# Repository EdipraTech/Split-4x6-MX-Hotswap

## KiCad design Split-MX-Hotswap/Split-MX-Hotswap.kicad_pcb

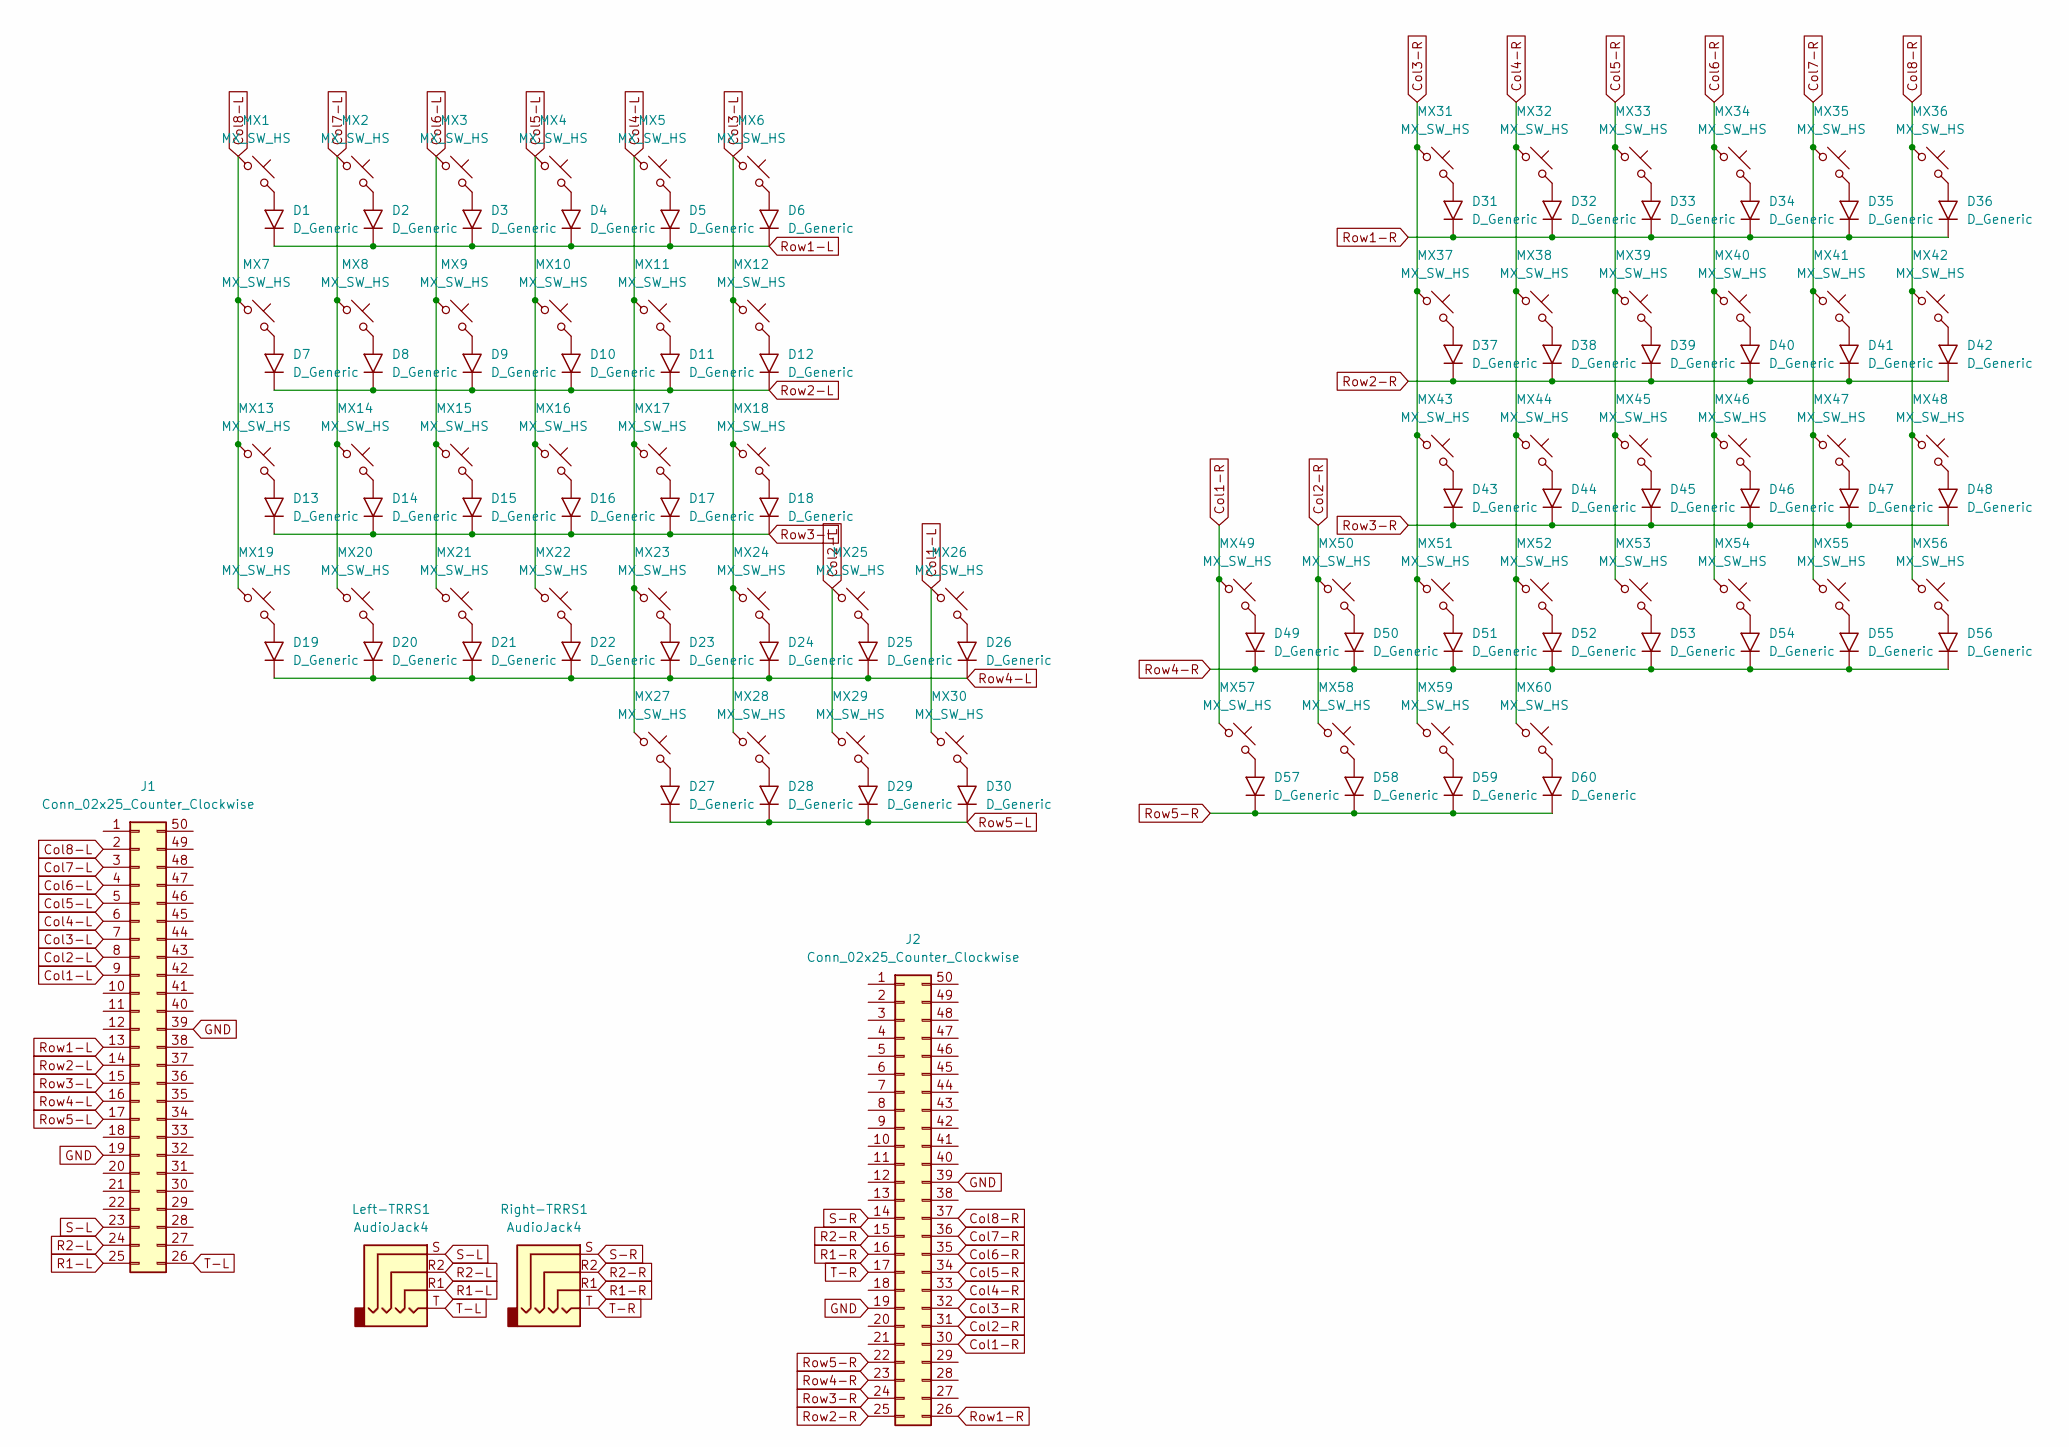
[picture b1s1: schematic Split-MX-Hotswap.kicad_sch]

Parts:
D1, D2, D3, D4, D5, D6, D7, D8, D9, D10, D11, D12, D13, D14, D15, D16, D17, D18, D19, D20, D21, D22, D23, D24, D25, D26, D27, D28, D29, D30, D31, D32, D33, D34, D35, D36, D37, D38, D39, D40, D41, D42, D43, D44, D45, D46, D47, D48, D49, D50, D51, D52, D53, D54, D55, D56, D57, D58, D59, D60: D_Generic; D_DO-35_P7.62mm_Horizontal
J1, J2: Conn_02x25_Counter_Clockwise; YAAJ_BluePill_SWD_2
Left-TRRS1: AudioJack4; CON_MJ-4PP-9
MX1, MX2, MX3, MX4, MX5, MX6, MX7, MX8, MX9, MX10, MX11, MX12, MX13, MX14, MX15, MX16, MX17, MX18, MX19, MX20, MX21, MX22, MX23, MX24, MX25, MX26, MX27, MX28, MX29, MX30, MX31, MX32, MX33, MX34, MX35, MX36, MX37, MX38, MX39, MX40, MX41, MX42, MX43, MX44, MX45, MX46, MX47, MX48, MX49, MX50, MX51, MX52, MX53, MX54, MX55, MX56, MX57, MX58, MX59, MX60: MX_SW_HS; SW_MX_HS_CPG151101S11_1u
Right-TRRS1: AudioJack4; CON_MJ-4PP-9

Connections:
Col1-L: J1.9, MX26.1, MX30.1
Col1-R: J2.30, MX49.1, MX57.1
Col2-L: J1.8, MX25.1, MX29.1
Col2-R: J2.31, MX50.1, MX58.1
Col3-L: J1.7, MX6.1, MX12.1, MX18.1, MX24.1, MX28.1
Col3-R: J2.32, MX31.1, MX37.1, MX43.1, MX51.1, MX59.1
Col4-L: J1.6, MX5.1, MX11.1, MX17.1, MX23.1, MX27.1
Col4-R: J2.33, MX32.1, MX38.1, MX44.1, MX52.1, MX60.1
Col5-L: J1.5, MX4.1, MX10.1, MX16.1, MX22.1
Col5-R: J2.34, MX33.1, MX39.1, MX45.1, MX53.1
Col6-L: J1.4, MX3.1, MX9.1, MX15.1, MX21.1
Col6-R: J2.35, MX34.1, MX40.1, MX46.1, MX54.1
Col7-L: J1.3, MX2.1, MX8.1, MX14.1, MX20.1
Col7-R: J2.36, MX35.1, MX41.1, MX47.1, MX55.1
Col8-L: J1.2, MX1.1, MX7.1, MX13.1, MX19.1
Col8-R: J2.37, MX36.1, MX42.1, MX48.1, MX56.1
GND: J1.19, J1.39, J2.19, J2.39
unnamed: D1.2 (A), MX1.2
unnamed: D2.2 (A), MX2.2
unnamed: D3.2 (A), MX3.2
unnamed: D4.2 (A), MX4.2
unnamed: D5.2 (A), MX5.2
unnamed: D6.2 (A), MX6.2
unnamed: D7.2 (A), MX7.2
unnamed: D8.2 (A), MX8.2
unnamed: D9.2 (A), MX9.2
unnamed: D10.2 (A), MX10.2
unnamed: D11.2 (A), MX11.2
unnamed: D12.2 (A), MX12.2
unnamed: D13.2 (A), MX13.2
unnamed: D14.2 (A), MX14.2
unnamed: D15.2 (A), MX15.2
unnamed: D16.2 (A), MX16.2
unnamed: D17.2 (A), MX17.2
unnamed: D18.2 (A), MX18.2
unnamed: D19.2 (A), MX19.2
unnamed: D20.2 (A), MX20.2
unnamed: D21.2 (A), MX21.2
unnamed: D22.2 (A), MX22.2
unnamed: D23.2 (A), MX23.2
unnamed: D24.2 (A), MX24.2
unnamed: D25.2 (A), MX25.2
unnamed: D26.2 (A), MX26.2
unnamed: D27.2 (A), MX27.2
unnamed: D28.2 (A), MX28.2
unnamed: D29.2 (A), MX29.2
unnamed: D30.2 (A), MX30.2
unnamed: D31.2 (A), MX31.2
unnamed: D32.2 (A), MX32.2
unnamed: D33.2 (A), MX33.2
unnamed: D34.2 (A), MX34.2
unnamed: D35.2 (A), MX35.2
unnamed: D36.2 (A), MX36.2
unnamed: D37.2 (A), MX37.2
unnamed: D38.2 (A), MX38.2
unnamed: D39.2 (A), MX39.2
unnamed: D40.2 (A), MX40.2
unnamed: D41.2 (A), MX41.2
unnamed: D42.2 (A), MX42.2
unnamed: D43.2 (A), MX43.2
unnamed: D44.2 (A), MX44.2
unnamed: D45.2 (A), MX45.2
unnamed: D46.2 (A), MX46.2
unnamed: D47.2 (A), MX47.2
unnamed: D48.2 (A), MX48.2
unnamed: D49.2 (A), MX49.2
unnamed: D50.2 (A), MX50.2
unnamed: D51.2 (A), MX51.2
unnamed: D52.2 (A), MX52.2
unnamed: D53.2 (A), MX53.2
unnamed: D54.2 (A), MX54.2
unnamed: D55.2 (A), MX55.2
unnamed: D56.2 (A), MX56.2
unnamed: D57.2 (A), MX57.2
unnamed: D58.2 (A), MX58.2
unnamed: D59.2 (A), MX59.2
unnamed: D60.2 (A), MX60.2
R1-L: J1.25, Left-TRRS1.R1
R1-R: J2.16, Right-TRRS1.R1
R2-L: J1.24, Left-TRRS1.R2
R2-R: J2.15, Right-TRRS1.R2
Row1-L: D1.1 (K), D2.1 (K), D3.1 (K), D4.1 (K), D5.1 (K), D6.1 (K), J1.13
Row1-R: D31.1 (K), D32.1 (K), D33.1 (K), D34.1 (K), D35.1 (K), D36.1 (K), J2.26
Row2-L: D7.1 (K), D8.1 (K), D9.1 (K), D10.1 (K), D11.1 (K), D12.1 (K), J1.14
Row2-R: D37.1 (K), D38.1 (K), D39.1 (K), D40.1 (K), D41.1 (K), D42.1 (K), J2.25
Row3-L: D13.1 (K), D14.1 (K), D15.1 (K), D16.1 (K), D17.1 (K), D18.1 (K), J1.15
Row3-R: D43.1 (K), D44.1 (K), D45.1 (K), D46.1 (K), D47.1 (K), D48.1 (K), J2.24
Row4-L: D19.1 (K), D20.1 (K), D21.1 (K), D22.1 (K), D23.1 (K), D24.1 (K), D25.1 (K), D26.1 (K), J1.16
Row4-R: D49.1 (K), D50.1 (K), D51.1 (K), D52.1 (K), D53.1 (K), D54.1 (K), D55.1 (K), D56.1 (K), J2.23
Row5-L: D27.1 (K), D28.1 (K), D29.1 (K), D30.1 (K), J1.17
Row5-R: D57.1 (K), D58.1 (K), D59.1 (K), D60.1 (K), J2.22
S-L: J1.23, Left-TRRS1.S
S-R: J2.14, Right-TRRS1.S
T-L: J1.26, Left-TRRS1.T
T-R: J2.17, Right-TRRS1.T

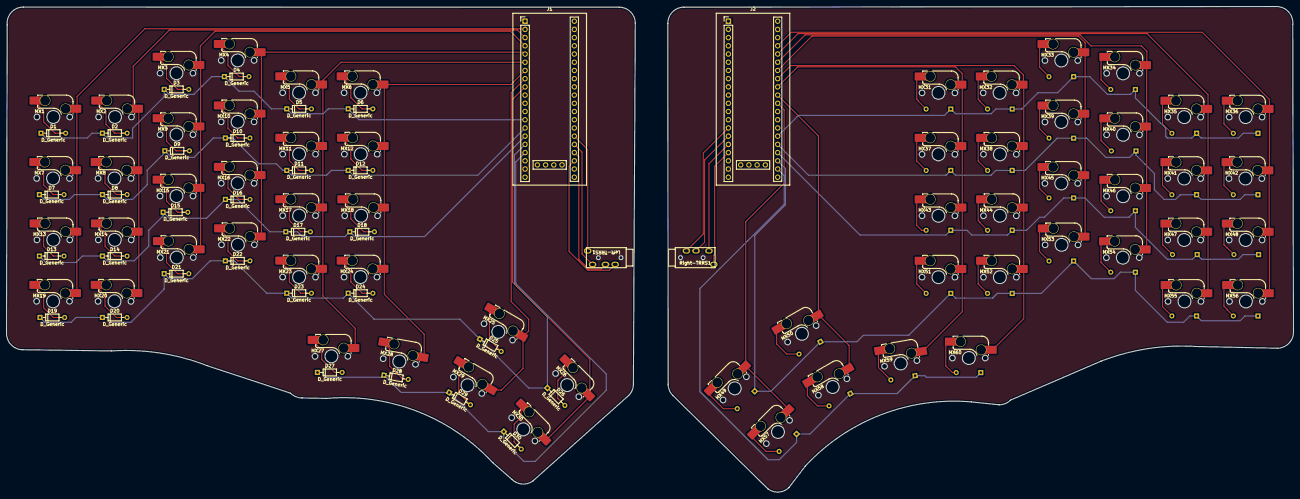
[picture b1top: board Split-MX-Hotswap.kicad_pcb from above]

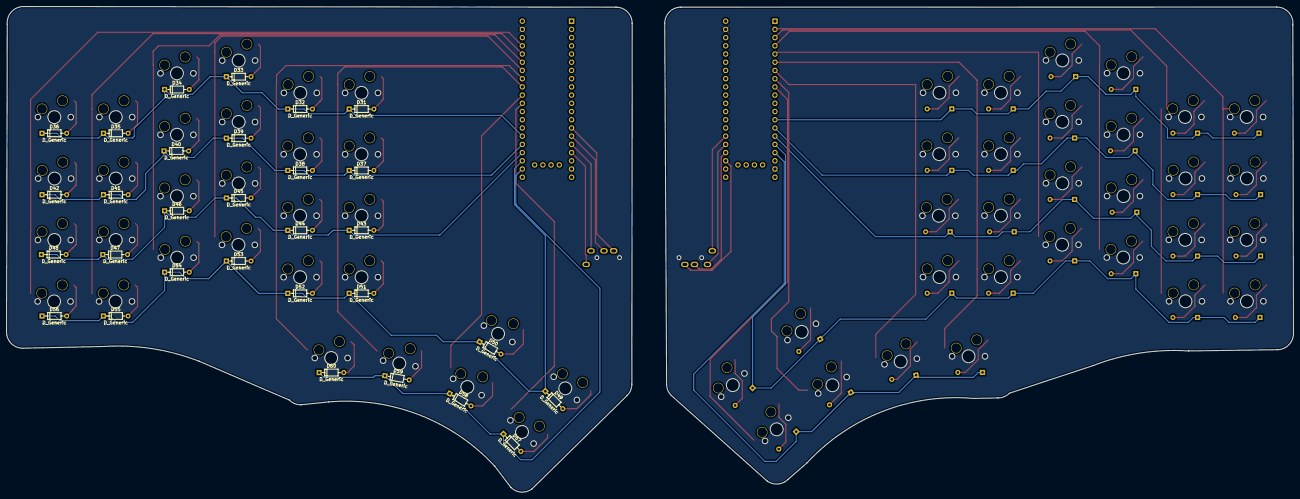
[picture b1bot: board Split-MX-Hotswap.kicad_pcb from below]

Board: 2 copper layers, 398.0 x 150.2 mm, 124 parts (30 on the bottom side), 95 nets.

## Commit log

2024-05-08 4x6 hot swap upload
2024-05-08 grounded board
